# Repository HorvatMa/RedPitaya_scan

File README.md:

# RedPitaya SiPM

RedPitaya system for image acquisition with scalar detector.

## Connection

OUT1 -- y galvo (Higher frequency)
OUT2 -- x galvo
IN1 -- y galvo position sensor
IN2 -- detector

The connection of the y galvo position sensor to the output is neccesary since at high frequancies (few 100 Hz) the lag between actual mirror position and signal output is significant (1/4 period @ 1 kHz) for Thorlabs GVS012.

## FPGA image

The FPGA program is written with vivado 2020.2 in verilog/SystemVerilog. The settings for generation of signals and acquisiton are handeled by writing to apropriate RAM positions inside the OS.

## Device Tree Overlay

The device tree overlay source file fpga.dtso is needed to tell the OS which parts of the memeory are mapped to FPGA functions. By applying the overlay with 
    ./apply_overlay.sh rp
OS then creates UIO devices which can be accessed and properly mapped inside the C application.

## C server

The server is written in C. It listens on port 5000 and supports commands:

- set_waveform {0 for OUT1 or 1 for OUT2} {WAVEFORM LENGTH} -- Sets the waveform length register. Command should be followed immediately by the same number int16 values which interpolate the availbale range +- 1 V.
- set_gen_decimation {0 for OUT1 or 1 for OUT2} {DECIMATION VALUE}
- start_gen -- Starts the generators
- stop_gen -- Stops the generators
- exit -- exits server
- start_acq -- Starts acquisition
- stop_acq -- Stops acquisition
- set_acq_decimation {DECIMATION VALUE} -- Sets acquisition decimation register
- set_int_decimation {DECIMATION VALUE} -- Sets integration decimation register

## Compiling

Server can be compiled by running the
    make server
command inside ./server directory.

fpga.dtbo needed in the apply_overlay.sh can be compiled from fpga.dtso using compile_dt.sh script.

## Workflow 

After setting both waveforms the generator decimation should be set. It sets the amount of the 125 MHz cycles which need to pass for the generator to move to the next waveform sample. After that the acquisition decimation should be set, which works the same as generators. (NOTE: too high of an acquisition will clog the TCP). The default value for integrator decimation is 1 which takes avery sameple into integration using parallelograms, it can be optionally changed. After that the generators can be started following by a start of acquisition. The server will the continiously stream samples (x: int16, y: int16, integrated_input uint32) (NOTE: integrator takes the input as an unsigned value, meaning that instead of +- 1 V in works as if the input was 0 V - 2 V). When finished the acquisition and generation can be stopped.

Test program of how the image is constructed is inside the ./client/src/image_test_2.py

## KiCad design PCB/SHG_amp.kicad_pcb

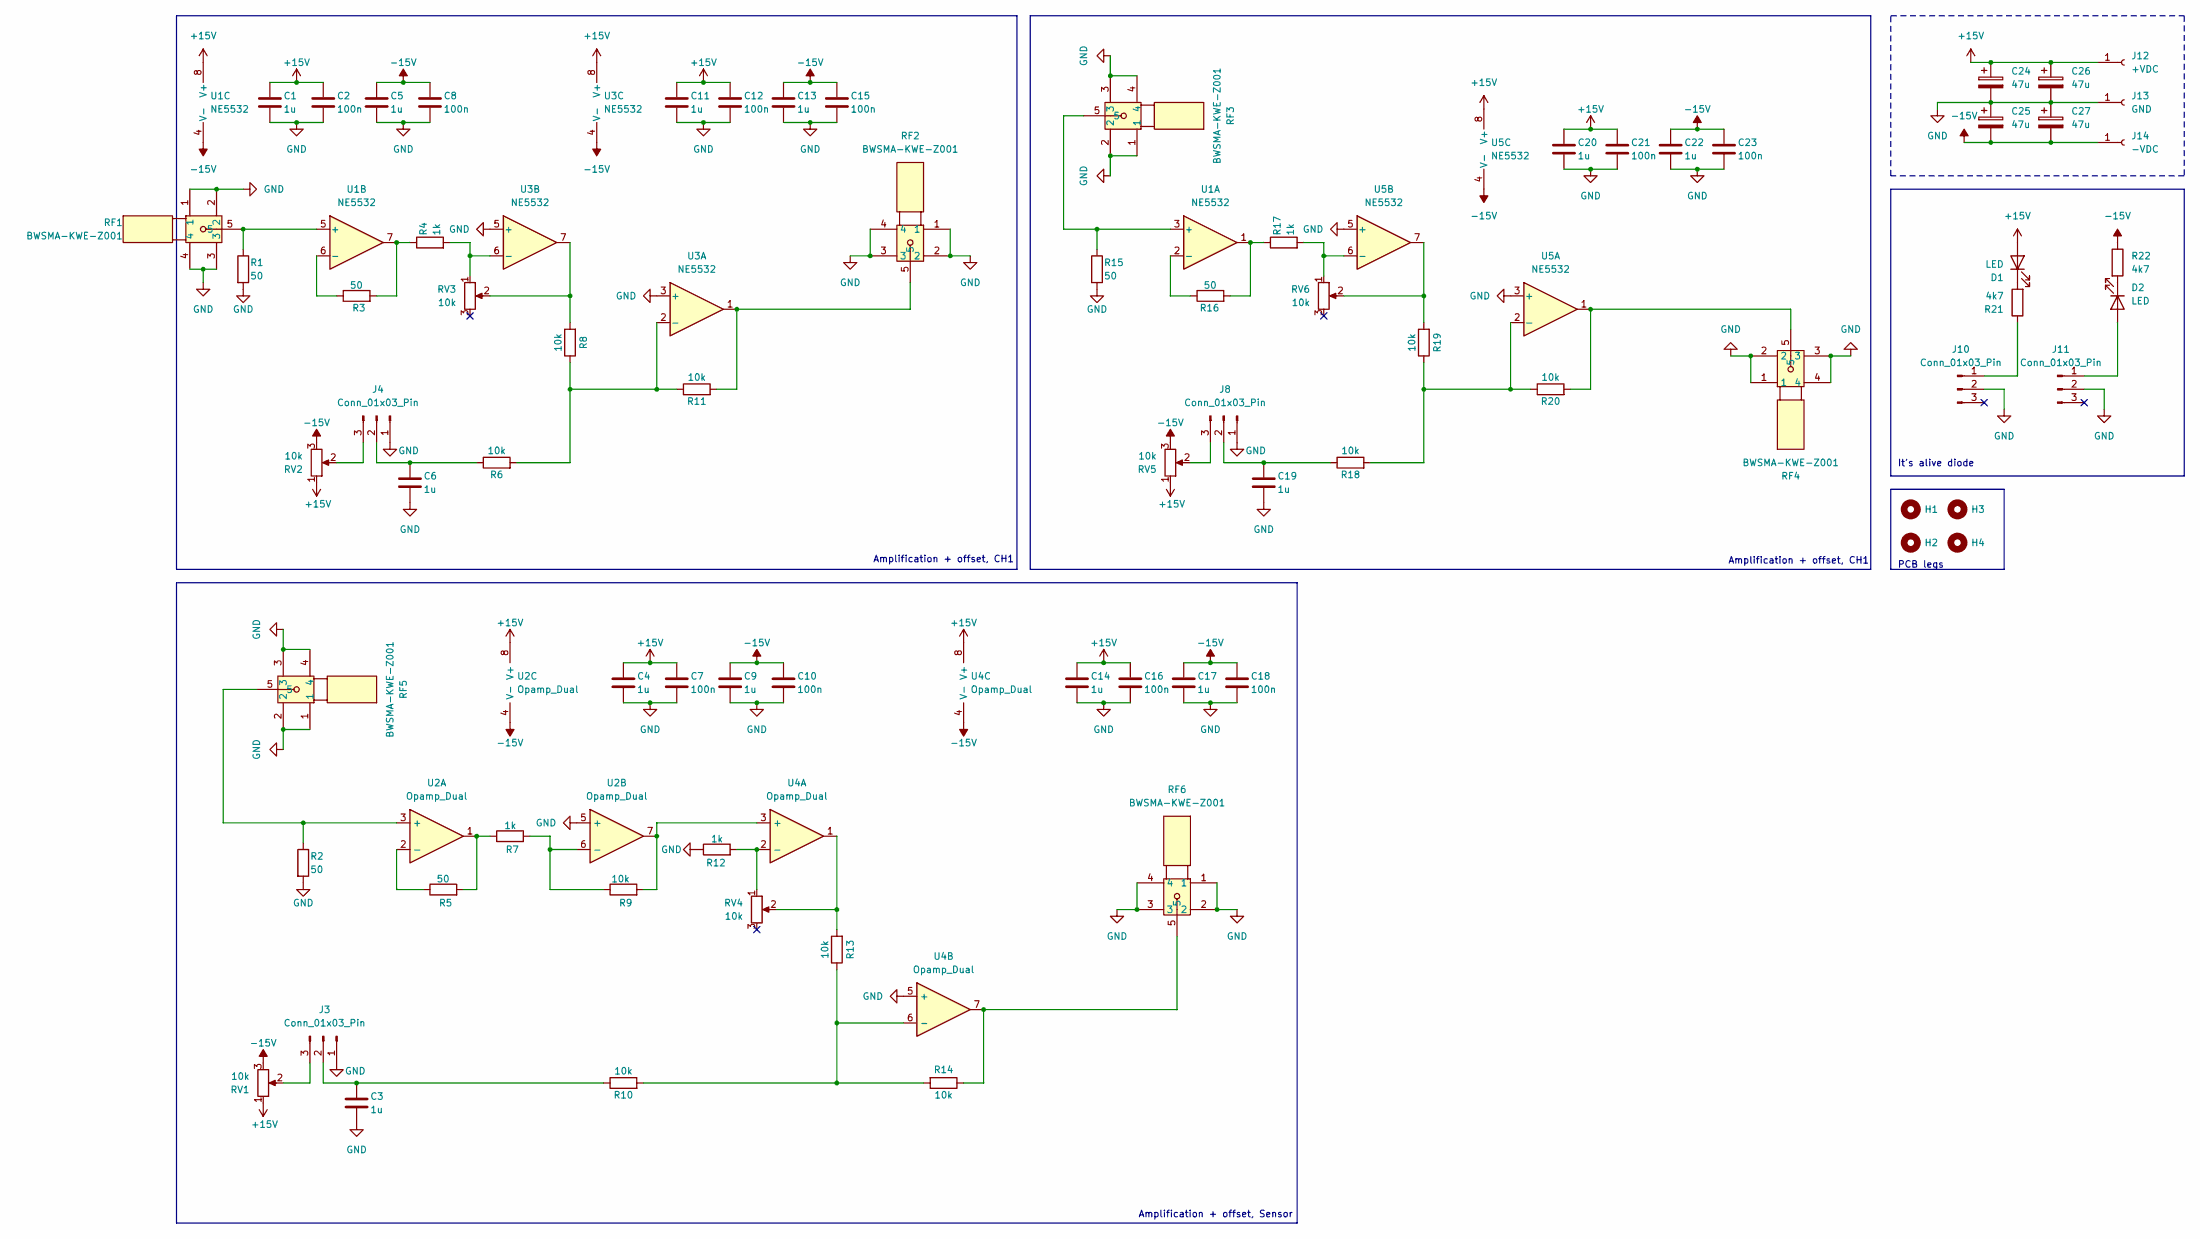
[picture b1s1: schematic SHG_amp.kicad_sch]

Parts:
C1, C3, C4, C5, C6, C9, C11, C13, C14, C17, C19, C20, C22: 1u; C_0805_2012Metric_Pad1.18x1.45mm_HandSolder
C2, C7, C8, C10, C12, C15, C16, C18, C21, C23: 100n; C_0805_2012Metric_Pad1.18x1.45mm_HandSolder
C24, C25, C26, C27: 47u; CP_Radial_D10.0mm_P5.00mm
D1, D2: LED; LED_0805_2012Metric_Pad1.15x1.40mm_HandSolder; LCSC C2297
H1, H2, H3, H4: MountingHole_3.2mm_M3_DIN965_Pad
J3, J4, J8, J10, J11: Conn_01x03_Pin; PinHeader_1x03_P2.54mm_Vertical
J12: +VDC; CONN_24.243_MTC
J13: GND; CONN_24.243_MTC
J14: -VDC; CONN_24.243_MTC
R1, R2, R3, R5, R15, R16: 50; R_0805_2012Metric_Pad1.20x1.40mm_HandSolder
R4, R7, R12, R17: 1k; R_0805_2012Metric_Pad1.20x1.40mm_HandSolder
R6, R8, R9, R10, R11, R13, R14, R18, R19, R20: 10k; R_0805_2012Metric_Pad1.20x1.40mm_HandSolder
R21, R22: 4k7; R_0805_2012Metric_Pad1.20x1.40mm_HandSolder
RF1, RF2, RF3, RF4, RF5, RF6: BWSMA-KWE-Z001; SMA-TH_BWSMA-KWE-Z001; LCSC Part C496551
RV1, RV2, RV3, RV4, RV5, RV6: 10k; Potentiometer_Bourns_PTV09A-1_Single_Vertical
U1, U3, U5: NE5532; SOIC-8_3.9x4.9mm_P1.27mm
U2, U4: Opamp_Dual; SOIC8_D_TEX

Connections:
+15V: C1.1, C2.1, C4.1, C7.1, C11.1, C12.1, C14.1, C16.1, C20.1, C21.1, C24.1, C26.1, D1.2 (A), J12.1, RV1.1, RV2.1, RV5.1, U1.8 (V+), U2.8 (V+), U3.8 (V+), U4.8 (V+), U5.8 (V+)
-15V: C5.1, C8.1, C9.1, C10.1, C13.1, C15.1, C17.1, C18.1, C22.1, C23.1, C25.2, C27.2, J14.1, R22.1, RV1.3, RV2.3, RV5.3, U1.4 (V-), U2.4 (V-), U3.4 (V-), U4.4 (V-), U5.4 (V-)
GND: C1.2, C2.2, C3.2, C4.2, C5.2, C6.2, C7.2, C8.2, C9.2, C10.2, C11.2, C12.2, C13.2, C14.2, C15.2, C16.2, C17.2, C18.2, C19.2, C20.2, C21.2, C22.2, C23.2, C24.2, C25.1, C26.2, C27.1, J3.1, J4.1, J8.1, J10.2, J11.2, J13.1, R1.2, R2.2, R12.1, R15.2, RF1.1, RF1.2, RF1.3, RF1.4, RF2.1, RF2.2, RF2.3, RF2.4, RF3.1, RF3.2, RF3.3, RF3.4, RF4.1, RF4.2, RF4.3, RF4.4, RF5.1, RF5.2, RF5.3, RF5.4, RF6.1, RF6.2, RF6.3, RF6.4, U2.5 (+), U3.3 (+), U3.5 (+), U4.5 (+), U5.3 (+), U5.5 (+)
unnamed: D1.1 (K), R21.2
unnamed: D2.2 (A), J11.1
unnamed: D2.1 (K), R22.2
unnamed: C3.1, J3.2, R10.1
unnamed: J3.3, RV1.2
unnamed: C6.1, J4.2, R6.1
unnamed: J4.3, RV2.2
unnamed: C19.1, J8.2, R18.1
unnamed: J8.3, RV5.2
unnamed: J10.1, R21.1
unnamed: R3.2, R4.1, U1.7
unnamed: R5.2, R7.1, U2.1
unnamed: R8.2, RV3.2, U3.7
unnamed: R11.2, RF2.5, U3.1
unnamed: R13.2, RV4.2, U4.1
unnamed: R14.1, RF6.5, U4.7
unnamed: R16.2, R17.1, U1.1
unnamed: R19.2, RV6.2, U5.7
unnamed: R20.2, RF4.5, U5.1
unnamed: R15.1, RF3.5, U1.3 (+)
unnamed: R16.1, U1.2 (-)
unnamed: R1.1, RF1.5, U1.5 (+)
unnamed: R3.1, U1.6 (-)
unnamed: R2.1, RF5.5, U2.3 (+)
unnamed: R5.1, U2.2 (-)
unnamed: R7.2, R9.1, U2.6 (-)
unnamed: R6.2, R8.1, R11.1, U3.2 (-)
unnamed: R4.2, RV3.1, U3.6 (-)
unnamed: R9.2, U2.7, U4.3 (+)
unnamed: R12.2, RV4.1, U4.2 (-)
unnamed: R10.2, R13.1, R14.2, U4.6 (-)
unnamed: R18.2, R19.1, R20.1, U5.2 (-)
unnamed: R17.2, RV6.1, U5.6 (-)

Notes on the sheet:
Amplification + offset, Sensor
PCB legs
Amplification + offset, CH1
It's alive diode

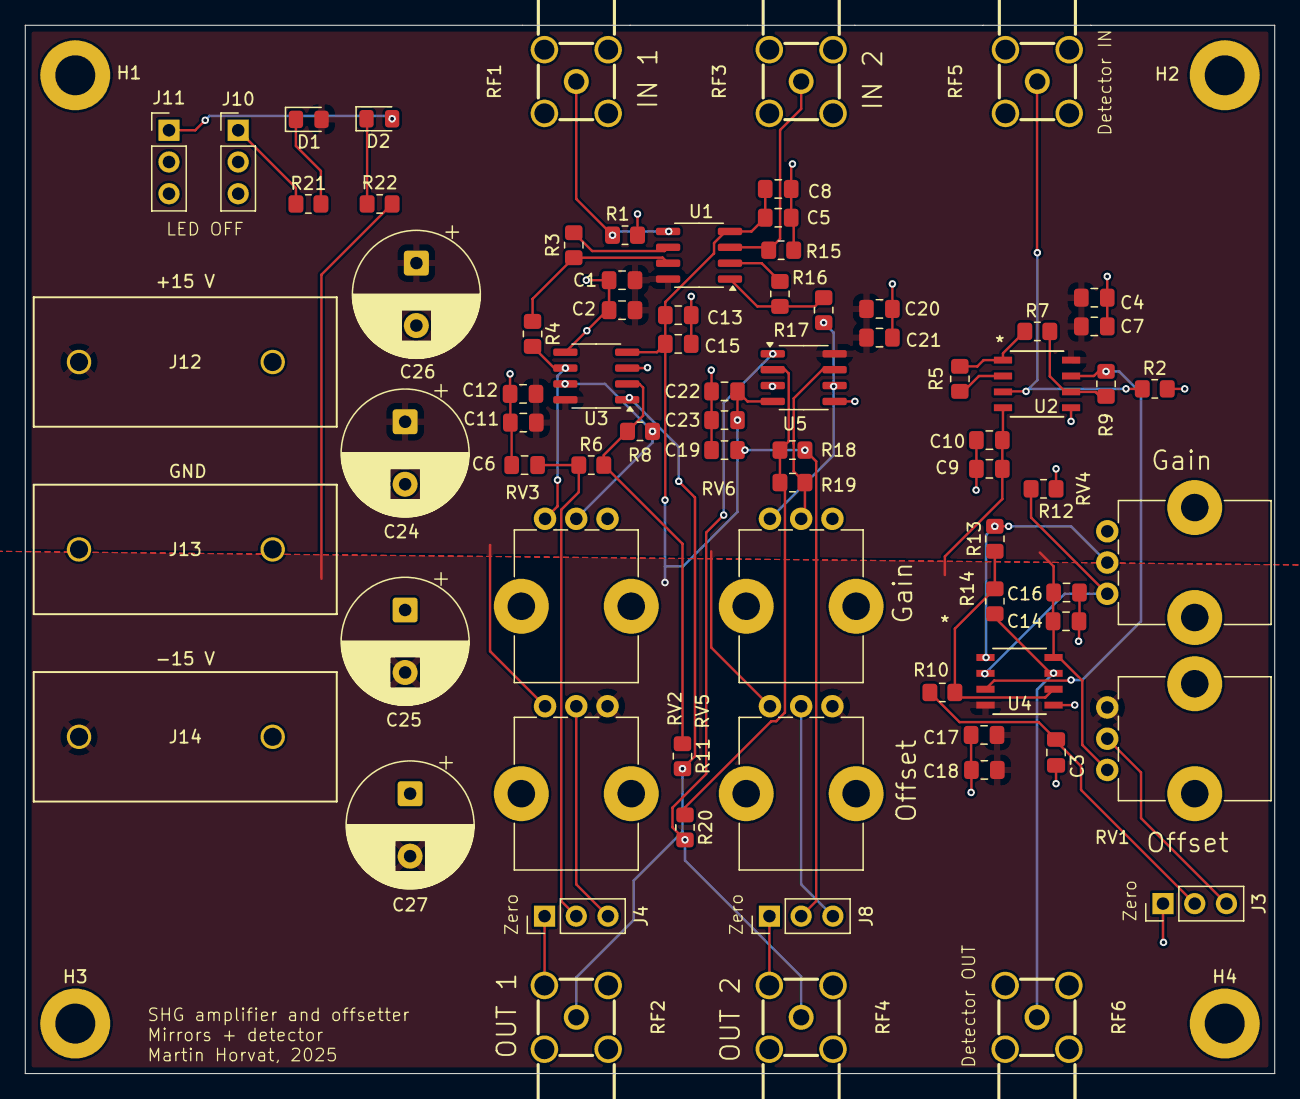
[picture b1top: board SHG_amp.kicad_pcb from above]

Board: 2 copper layers, 100.0 x 83.9 mm, 80 parts (0 on the bottom side), 36 nets.

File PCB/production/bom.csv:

Designator,Footprint,Quantity,Value,LCSC Part #
"C1, C11, C13, C14, C17, C19, C20, C22, C3, C4, C5, C6, C9",0805,13,1u,
"C10, C12, C15, C16, C18, C2, C21, C23, C7, C8",0805,10,100n,
"C24, C25, C26, C27",CP_Radial_D10.0mm_P5.00mm,4,47u,
"D1, D2",0805,2,LED,C2297
"H1, H2, H3, H4",MountingHole_3.2mm_M3_DIN965_Pad,4,~,
"J10, J11, J3, J4, J8",PinHeader_1x03_P2.54mm_Vertical,5,Conn_01x03_Pin,
J12,CONN_24.243_MTC,1,+15 V,
J13,CONN_24.243_MTC,1,GND,
J14,CONN_24.243_MTC,1,-15 V,
"R1, R15, R16, R2, R3, R5",0805,6,50,
"R10, R11, R13, R14, R18, R19, R20, R6, R8, R9",0805,10,10k,
"R12, R17, R4, R7",0805,4,1k,
"R21, R22",0805,2,4k7,
"RF1, RF2, RF3, RF4, RF5, RF6",SMA-TH_BWSMA-KWE-Z001,6,BWSMA-KWE-Z001,C496551
"RV1, RV2, RV3, RV4, RV5, RV6",Potentiometer_Bourns_PTV09A-1_Single_Vertical,6,10k,
"U1, U3, U5",SOIC-8_3.9x4.9mm_P1.27mm,3,NE5532,
"U2, U4",SOIC8_D_TEX,2,Opamp_Dual,
